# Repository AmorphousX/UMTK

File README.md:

# UMTK
Code for running UMTK

## Indicator LED

- Slow Flash: Not Connected
- Fast Flash: Running
- ON: Jogging
- OFF: Standby

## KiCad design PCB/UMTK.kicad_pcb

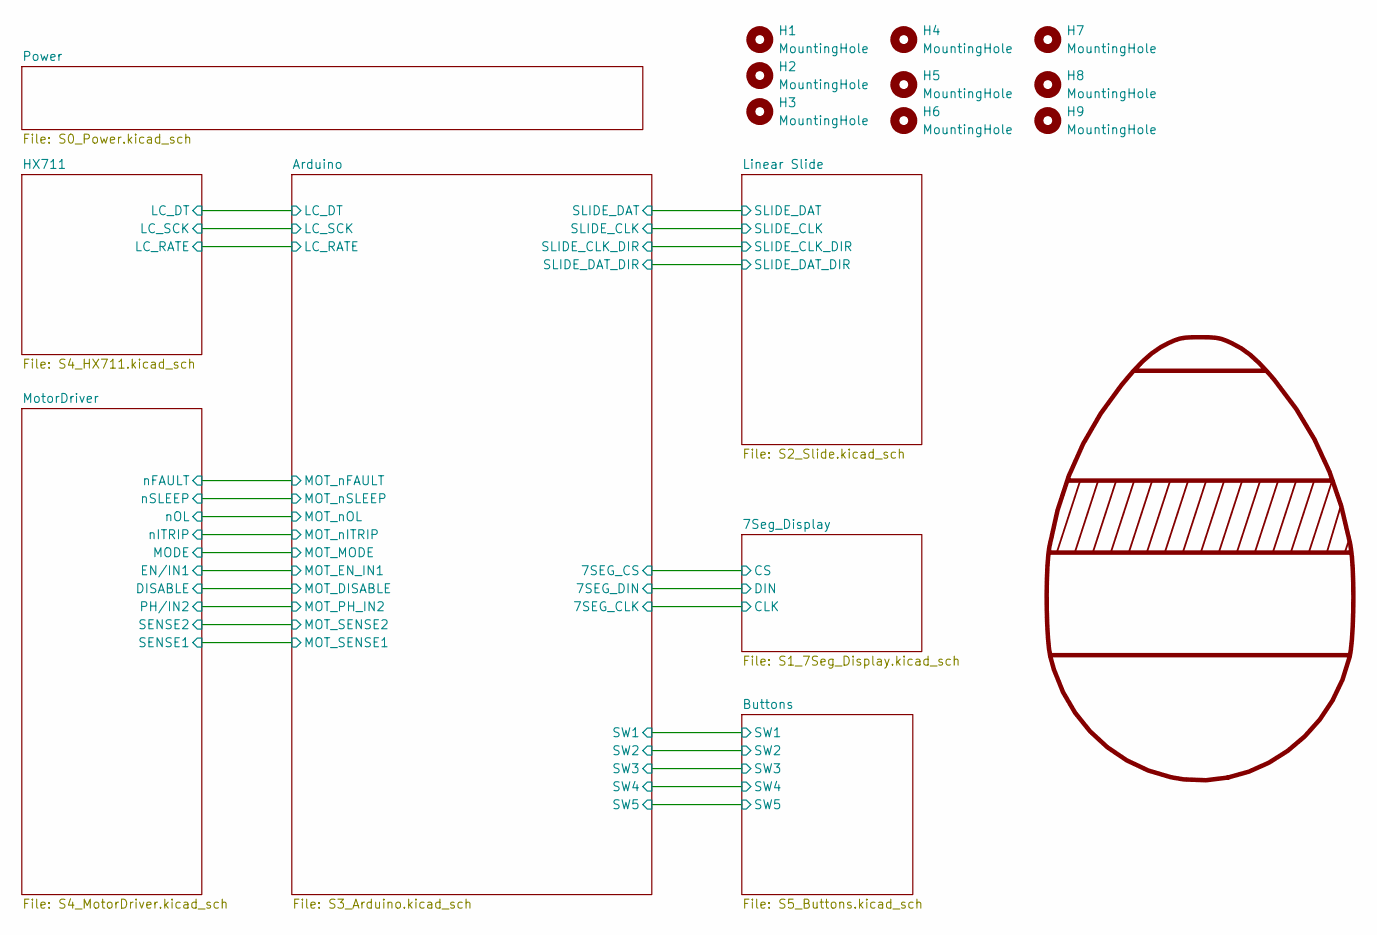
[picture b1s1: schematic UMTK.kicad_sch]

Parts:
G1: Tensile Cat
H1, H2, H3, H4, H5, H6, H7, H8, H9: MountingHole; MountingHole_4mm

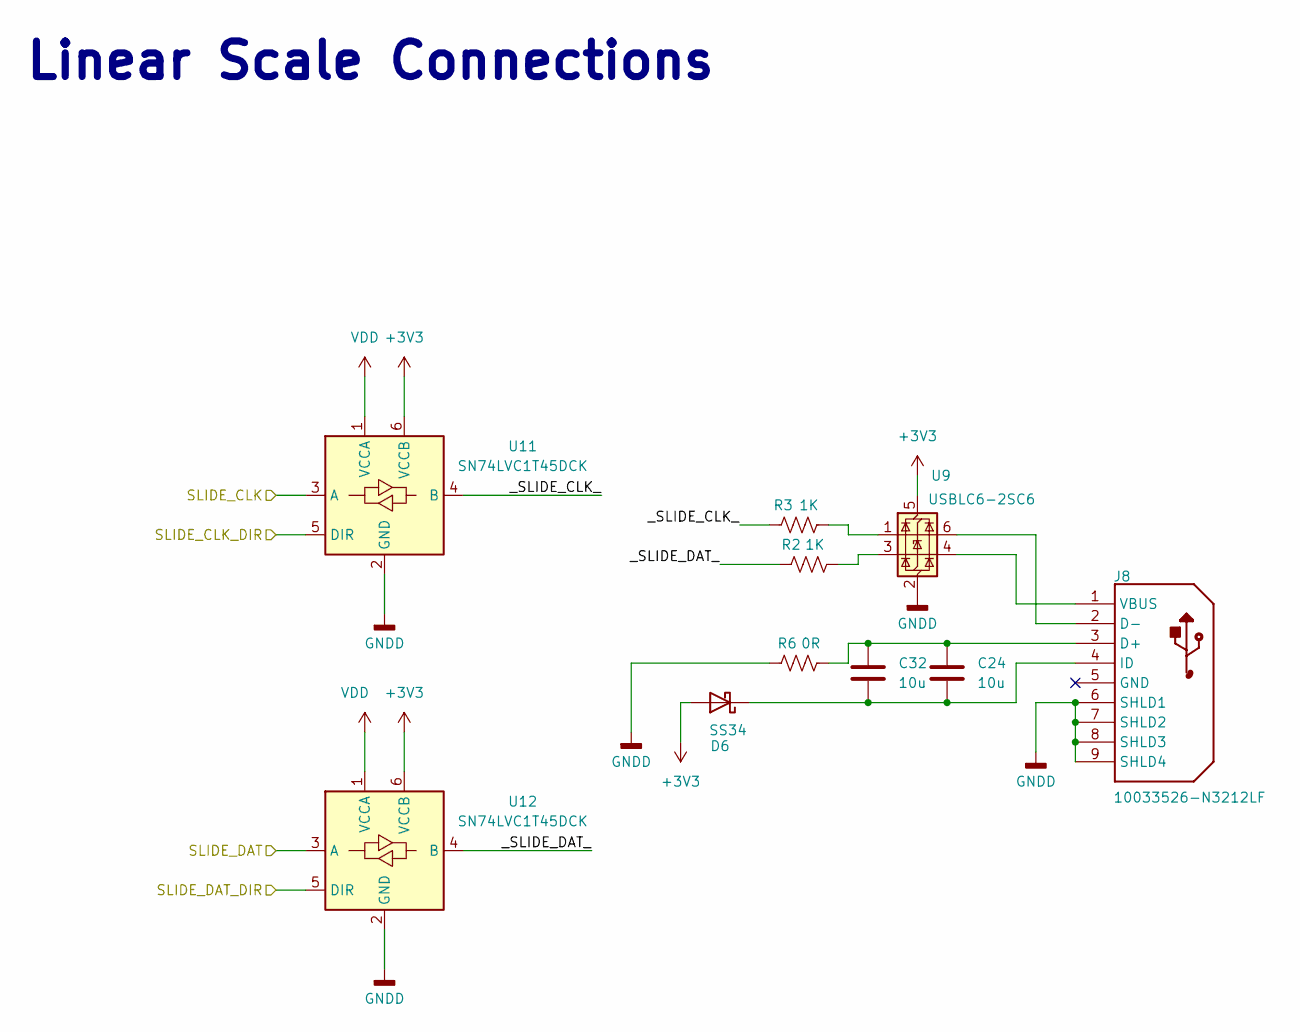
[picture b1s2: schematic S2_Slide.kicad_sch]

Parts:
C24, C32: 10u; C_0805_2012Metric
D6: SS34; D_SMA
J8: 10033526-N3212LF; USB_Mini-B_Wuerth_65100516121_Horizontal; FLAMMABILITY RATING UL 94 V-0; PARTNUMBER 10033526-N3212LF
R2, R3: 1K; R_0603_1608Metric
R6: 0R; R_0603_1608Metric
U9: USBLC6-2SC6; SOT-23-6
U11, U12: SN74LVC1T45DCK; SOT-363_SC-70-6

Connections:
+3V3: D6.2 (A), U9.5 (VBUS), U11.6 (VCCB), U12.6 (VCCB); also elsewhere on the board
+5V: U11.1 (VCCA), U12.1 (VCCA); also elsewhere on the board
/Arduino/D3: U11.3 (A); also elsewhere on the board
/Arduino/D4: U12.3 (A); also elsewhere on the board
/Arduino/D23: U11.5 (DIR); also elsewhere on the board
/Arduino/D24: U12.5 (DIR); also elsewhere on the board
/Linear Slide/_SLIDE_CLK_: R3.1, U11.4 (B)
/Linear Slide/_SLIDE_DAT_: R2.1, U12.4 (B)
GNDA: J8.6 (SHLD1), J8.7 (SHLD2), J8.8 (SHLD3), J8.9 (SHLD4), R6.1, U9.2 (GND), U11.2 (GND), U12.2 (GND); also elsewhere on the board
unnamed: C24.1, C32.1, D6.1 (K), J8.4 (ID)
unnamed: C24.2, C32.2, J8.3 (D+), R6.2
unnamed: J8.2 (D-), U9.6 (I/O1)
unnamed: J8.1 (VBUS), U9.4 (I/O2)
unnamed: R2.2, U9.3 (I/O2)
unnamed: R3.2, U9.1 (I/O1)

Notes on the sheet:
Linear Scale Connections

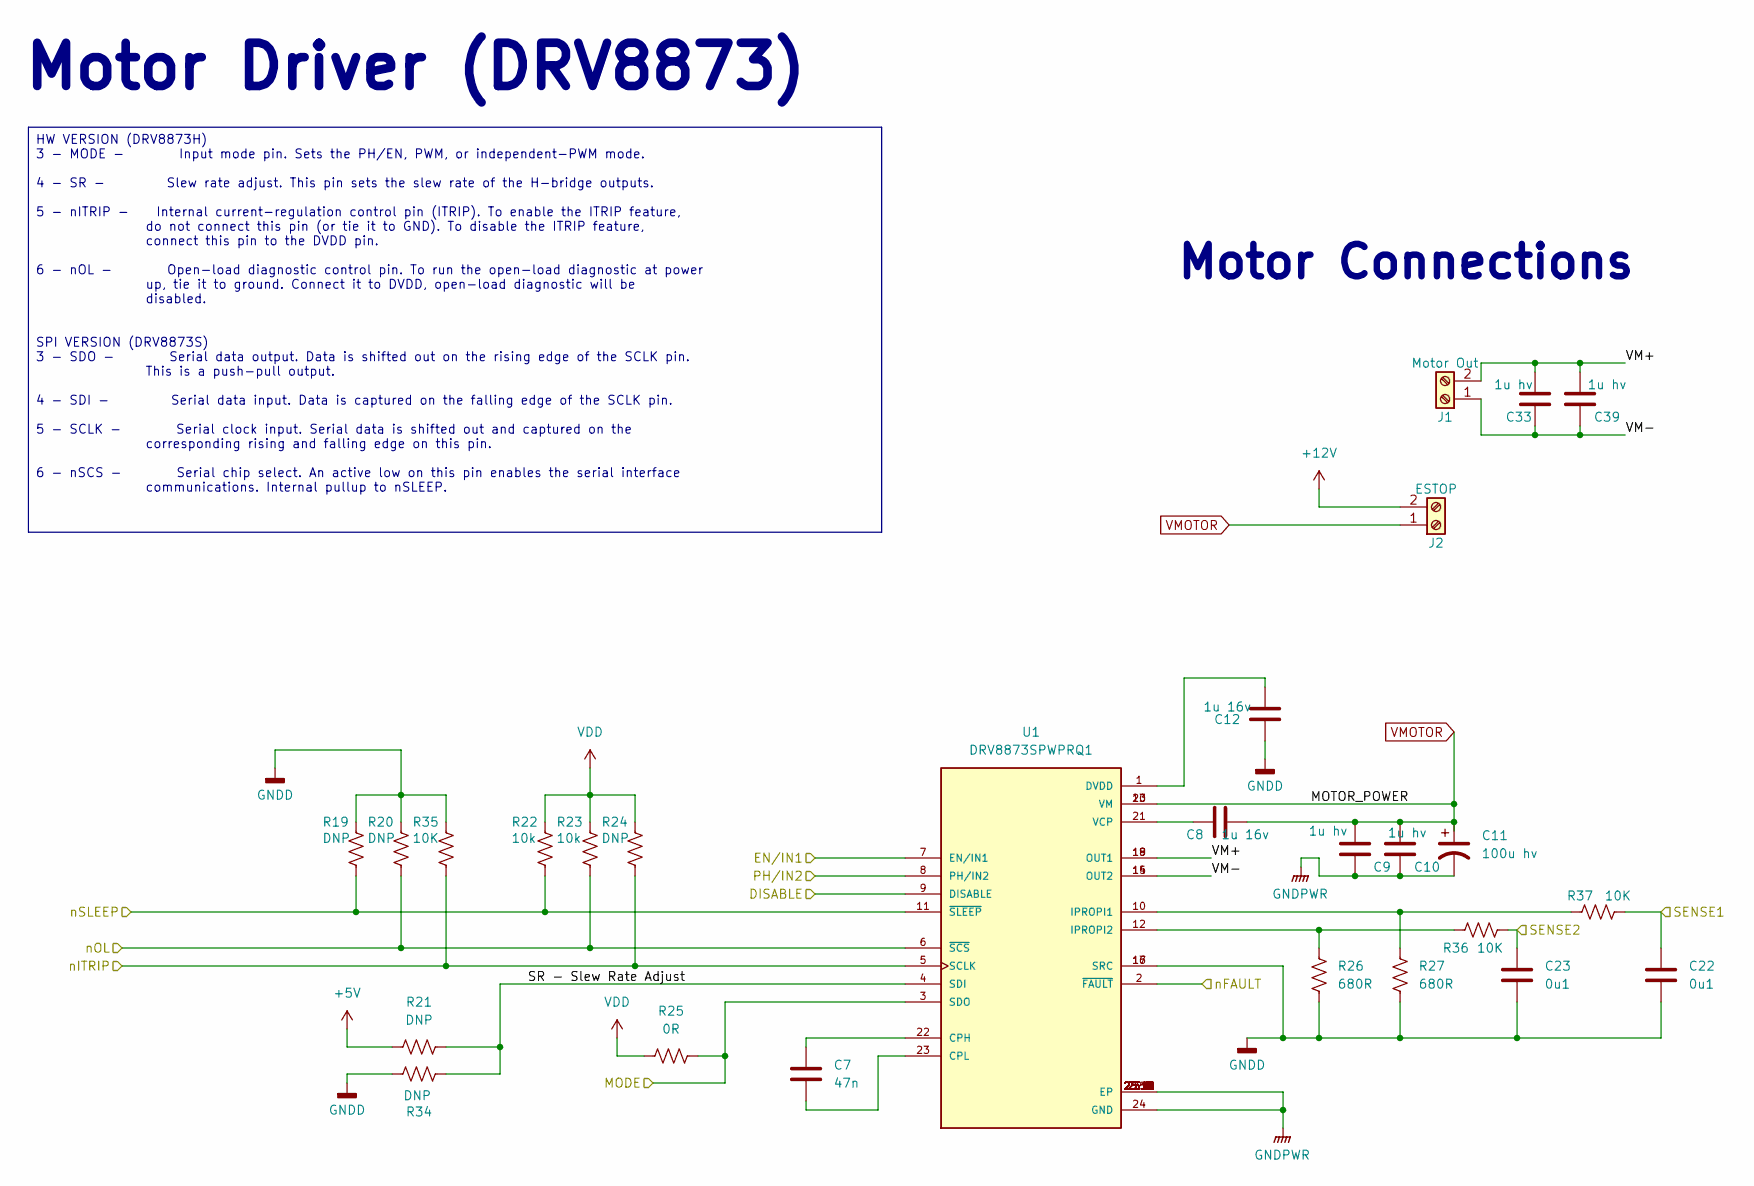
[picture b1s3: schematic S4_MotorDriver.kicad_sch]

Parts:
C7: 47n; C_0603_1608Metric
C8, C12: 1u 16v; C_0603_1608Metric
C9, C10, C33, C39: 1u hv; C_1206_3216Metric
C11: 100u hv; CP_Elec_10x10.5
C22, C23: 0u1; C_0603_1608Metric
J1: Motor Out; PhoenixContact_MC_1,5_2-G-3.81_1x02_P3.81mm_Horizontal
J2: ESTOP; PhoenixContact_MSTBA_2,5_2-G-5,08_1x02_P5.08mm_Horizontal
R19, R20, R21, R24, R34: DNP; R_0603_1608Metric
R22, R23: 10k; R_0603_1608Metric
R25: 0R; R_0603_1608Metric
R26, R27: 680R; R_0603_1608Metric
R35, R36, R37: 10K; R_0603_1608Metric
U1: DRV8873SPWPRQ1; HTSSOP-24-1EP_4.4x7.8mm_P0.65mm_EP3.4x7.8mm_Mask2.4x4.68mm_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; PARTREV A

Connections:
+5V: R21.2, R22.2, R23.2, R24.2, R25.1; also elsewhere on the board
+12V: J2.2; also elsewhere on the board
/Arduino/A2: C22.1, R37.2; also elsewhere on the board
/Arduino/A3: C23.1, R36.2; also elsewhere on the board
/Arduino/D7: U1.9 (DISABLE); also elsewhere on the board
/Arduino/D8: U1.7 (EN/IN1); also elsewhere on the board
/Arduino/D9: U1.8 (PH/IN2); also elsewhere on the board
/Arduino/D10: R24.1, R35.1, U1.5 (SCLK); also elsewhere on the board
/Arduino/D11: R20.1, R23.1, U1.6 (~SCS); also elsewhere on the board
/Arduino/D12: U1.2 (~FAULT); also elsewhere on the board
/Arduino/D14: R19.1, R22.1, U1.11 (~SLEEP); also elsewhere on the board
/Arduino/D22: R25.2, U1.3 (SDO); also elsewhere on the board
/MotorDriver/SR - Slew Rate Adjust: R21.1, R34.2, U1.4 (SDI)
/MotorDriver/VM+: C33.2, C39.2, J1.2, U1.18 (OUT1), U1.19 (OUT1)
/MotorDriver/VM-: C33.1, C39.1, J1.1, U1.14 (OUT2), U1.15 (OUT2)
GNDA: C9.1, C10.1, C11.2, C12.2, C22.2, C23.2, R19.2, R20.2, R26.1, R27.1, R34.1, R35.2, U1.16 (SRC), U1.17 (SRC), U1.24 (GND), U1.25 (EP), U1.25.1 (EP), U1.25.2 (EP), U1.25.3 (EP), U1.25.4 (EP), U1.25.5 (EP), U1.25.6 (EP), U1.25.7 (EP), U1.25.8 (EP), U1.25.9 (EP), U1.25.10 (EP), U1.25.11 (EP), U1.25.12 (EP), U1.25.13 (EP), U1.25.14 (EP), U1.25.15 (EP), U1.25.16 (EP), U1.25.17 (EP), U1.25.18 (EP); also elsewhere on the board
unnamed: C7.1, U1.22 (CPH)
unnamed: C7.2, U1.23 (CPL)
unnamed: C12.1, U1.1 (DVDD)
unnamed: R27.2, R37.1, U1.10 (IPROPI1)
unnamed: R26.2, R36.1, U1.12 (IPROPI2)
unnamed: C8.1, U1.21 (VCP)
VMOTOR: C8.2, C9.2, C10.2, C11.1, J2.1, U1.13 (VM), U1.20 (VM); also elsewhere on the board

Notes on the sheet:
Motor Connections
Motor Driver (DRV8873)
HW VERSION (DRV8873H) 3 - MODE - Input mode pin. Sets the PH/EN, PWM, or independent-PWM mode. 4 - SR - Slew rate adjust. This pin sets the slew rate of the H-bridge outputs. 5 - nITRIP - Internal current-regulation control pin (ITRIP). To enable the ITRIP feature, do not connect this pin (or tie i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

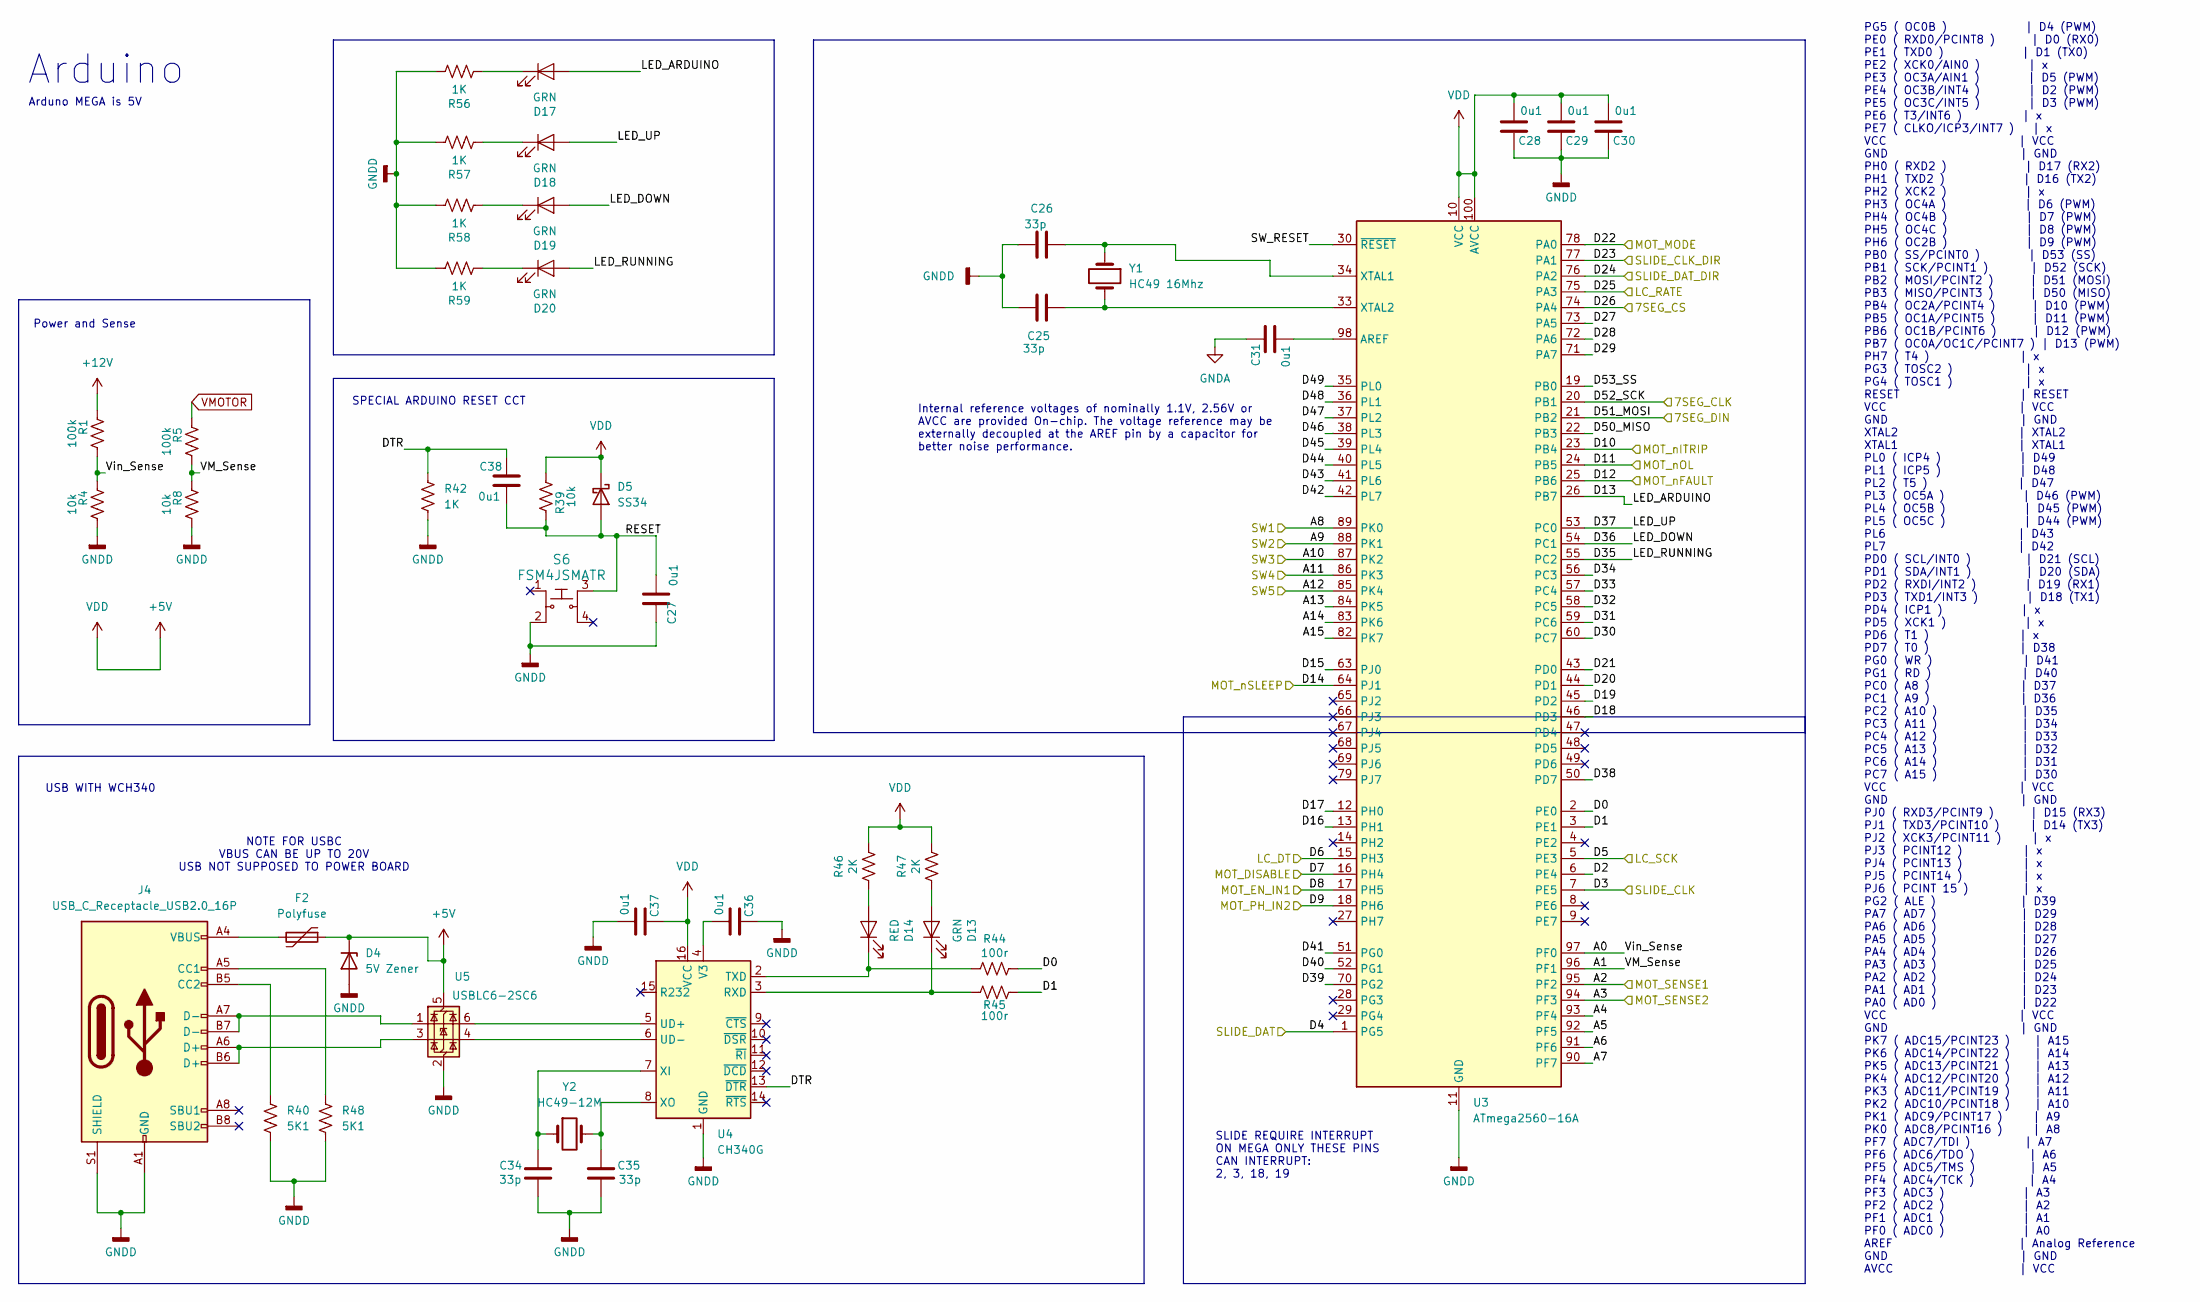
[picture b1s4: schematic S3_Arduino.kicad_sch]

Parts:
C25, C26, C34, C35: 33p; C_0603_1608Metric
C27, C28, C29, C30, C31, C36, C37, C38: 0u1; C_0603_1608Metric
D4: 5V Zener; D_SOD-523
D5: SS34; D_SMA
D13, D17, D18, D19, D20: GRN; LED_0603_1608Metric
D14: RED; LED_0603_1608Metric
F2: Polyfuse; Fuse_1206_3216Metric
J4: USB_C_Receptacle_USB2.0_16P; USB_C_Receptacle_HCTL_HC-TYPE-C-16P-01A
R1, R5: 100k; R_0603_1608Metric
R4, R8, R39: 10k; R_0603_1608Metric
R40, R48: 5K1; R_0603_1608Metric
R42, R56, R57, R58, R59: 1K; R_0603_1608Metric
R44, R45: 100r; R_0603_1608Metric
R46, R47: 2K; R_0603_1608Metric
S6: FSM4JSMATR; Switch_Tactile_SMD_6x6mm; MPN FSM4JSMATR; Digi-Key_PN 450-1759-1-ND
U3: ATmega2560-16A; TQFP-100_14x14mm_P0.5mm
U4: CH340G; SOIC-16_3.9x9.9mm_P1.27mm
U5: USBLC6-2SC6; SOT-23-6
Y1: HC49 16Mhz; Crystal_SMD_HC49-SD
Y2: HC49-12M; Crystal_SMD_HC49-SD

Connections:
+5V: C28.2, C29.2, C30.2, C37.1, D4.1 (K), D5.1 (K), F2.1, R39.2, R46.2, R47.2, U3.10 (VCC), U3.31 (VCC), U3.61 (VCC), U3.80 (VCC), U3.100 (AVCC), U4.16 (VCC), U5.5 (VBUS); also elsewhere on the board
+12V: R1.1; also elsewhere on the board
/Arduino/A0: R1.2, R4.1, U3.97 (PF0)
/Arduino/A1: R5.2, R8.1, U3.96 (PF1)
/Arduino/A2: U3.95 (PF2); also elsewhere on the board
/Arduino/A3: U3.94 (PF3); also elsewhere on the board
/Arduino/A4: U3.93 (PF4)
/Arduino/A5: U3.92 (PF5)
/Arduino/A6: U3.91 (PF6)
/Arduino/A7: U3.90 (PF7)
/Arduino/A8: U3.89 (PK0); also elsewhere on the board
/Arduino/A9: U3.88 (PK1); also elsewhere on the board
/Arduino/A10: U3.87 (PK2); also elsewhere on the board
/Arduino/A11: U3.86 (PK3); also elsewhere on the board
/Arduino/A12: U3.85 (PK4); also elsewhere on the board
/Arduino/A13: U3.84 (PK5)
/Arduino/A14: U3.83 (PK6)
/Arduino/A15: U3.82 (PK7)
/Arduino/D0: R44.2, U3.2 (PE0)
/Arduino/D1: R45.2, U3.3 (PE1)
/Arduino/D2: U3.6 (PE4)
/Arduino/D3: U3.7 (PE5); also elsewhere on the board
/Arduino/D4: U3.1 (PG5); also elsewhere on the board
/Arduino/D5: U3.5 (PE3); also elsewhere on the board
/Arduino/D6: U3.15 (PH3); also elsewhere on the board
/Arduino/D7: U3.16 (PH4); also elsewhere on the board
/Arduino/D8: U3.17 (PH5); also elsewhere on the board
/Arduino/D9: U3.18 (PH6); also elsewhere on the board
/Arduino/D10: U3.23 (PB4); also elsewhere on the board
/Arduino/D11: U3.24 (PB5); also elsewhere on the board
/Arduino/D12: U3.25 (PB6); also elsewhere on the board
/Arduino/D13: D17.2 (A), U3.26 (PB7)
/Arduino/D14: U3.64 (PJ1); also elsewhere on the board
/Arduino/D15: U3.63 (PJ0)
/Arduino/D16: U3.13 (PH1)
/Arduino/D17: U3.12 (PH0)
/Arduino/D18: U3.46 (PD3)
/Arduino/D19: U3.45 (PD2)
/Arduino/D20: U3.44 (PD1)
/Arduino/D21: U3.43 (PD0)
/Arduino/D22: U3.78 (PA0); also elsewhere on the board
/Arduino/D23: U3.77 (PA1); also elsewhere on the board
/Arduino/D24: U3.76 (PA2); also elsewhere on the board
/Arduino/D25: U3.75 (PA3); also elsewhere on the board
/Arduino/D26: U3.74 (PA4); also elsewhere on the board
/Arduino/D27: U3.73 (PA5)
/Arduino/D28: U3.72 (PA6)
/Arduino/D29: U3.71 (PA7)
/Arduino/D30: U3.60 (PC7)
/Arduino/D31: U3.59 (PC6)
/Arduino/D32: U3.58 (PC5)
/Arduino/D33: U3.57 (PC4)
/Arduino/D34: U3.56 (PC3)
/Arduino/D35: D20.2 (A), U3.55 (PC2)
/Arduino/D36: D19.2 (A), U3.54 (PC1)
/Arduino/D37: D18.2 (A), U3.53 (PC0)
/Arduino/D38: U3.50 (PD7)
/Arduino/D39: U3.70 (PG2)
/Arduino/D40: U3.52 (PG1)
/Arduino/D41: U3.51 (PG0)
/Arduino/D42: U3.42 (PL7)
/Arduino/D43: U3.41 (PL6)
/Arduino/D44: U3.40 (PL5)
/Arduino/D45: U3.39 (PL4)
/Arduino/D46: U3.38 (PL3)
/Arduino/D47: U3.37 (PL2)
/Arduino/D48: U3.36 (PL1)
/Arduino/D49: U3.35 (PL0)
/Arduino/D50_MISO: U3.22 (PB3)
/Arduino/D51_MOSI: U3.21 (PB2); also elsewhere on the board
/Arduino/D52_SCK: U3.20 (PB1); also elsewhere on the board
/Arduino/D53_SS: U3.19 (PB0)
/Arduino/DTR: C38.1, R42.1, U4.13 (~DTR)
/Arduino/RESET: C27.2, C38.2, D5.2 (A), R39.1, S6.3
/Arduino/SW_RESET: U3.30 (~RESET)
GNDA: C25.1, C26.1, C27.1, C28.1, C29.1, C30.1, C31.1, C34.1, C35.1, C36.1, C37.2, D4.2 (A), J4.A1 (GND), J4.A12 (GND), J4.B1 (GND), J4.B12 (GND), J4.S1 (SHIELD), R4.2, R8.2, R40.2, R42.2, R48.2, R56.1, R57.1, R58.1, R59.1, S6.2, U3.11 (GND), U3.32 (GND), U3.62 (GND), U3.81 (GND), U3.99 (GND), U4.1 (GND), U5.2 (GND); also elsewhere on the board
unnamed: D13.2 (A), R47.1
unnamed: D13.1 (K), R45.1, U4.3 (RXD)
unnamed: D14.2 (A), R46.1
unnamed: D14.1 (K), R44.1, U4.2 (TXD)
unnamed: D17.1 (K), R56.2
unnamed: D18.1 (K), R57.2
unnamed: D19.1 (K), R58.2
unnamed: D20.1 (K), R59.2
unnamed: F2.2, J4.A4 (VBUS), J4.A9 (VBUS), J4.B4 (VBUS), J4.B9 (VBUS)
unnamed: J4.A5 (CC1), R48.1
unnamed: J4.B5 (CC2), R40.1
unnamed: J4.A6 (D+), J4.B6 (D+), U5.3 (I/O2)
unnamed: J4.A7 (D-), J4.B7 (D-), U5.1 (I/O1)
unnamed: C31.2, U3.98 (AREF)
unnamed: C26.2, U3.34 (XTAL1), Y1.1
unnamed: C25.2, U3.33 (XTAL2), Y1.2
unnamed: U4.5 (UD+), U5.6 (I/O1)
unnamed: U4.6 (UD-), U5.4 (I/O2)
unnamed: C36.2, U4.4 (V3)
unnamed: C34.2, U4.7 (XI), Y2.1
unnamed: C35.2, U4.8 (XO), Y2.2
VMOTOR: R5.1; also elsewhere on the board

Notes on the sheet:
Internal reference voltages of nominally 1.1V, 2.56V or AVCC are provided On-chip. The voltage reference may be externally decoupled at the AREF pin by a capacitor for better noise performance.
NOTE FOR USBC VBUS CAN BE UP TO 20V USB NOT SUPPOSED TO POWER BOARD
Arduno MEGA is 5V
Arduino
SLIDE REQUIRE INTERRUPT ON MEGA ONLY THESE PINS CAN INTERRUPT: 2, 3, 18, 19
USB WITH WCH340
SPECIAL ARDUINO RESET CCT
Power and Sense
PG5 ( OC0B ) | D4 (PWM) PE0 ( RXD0/PCINT8 ) | D0 (RX0) PE1 ( TXD0 ) | D1 (TX0) PE2 ( XCK0/AIN0 ) | x PE3 ( OC3A/AIN1 ) | D5 (PWM) PE4 ( OC3B/INT4 ) | D2 (PWM) PE5 ( OC3C/INT5 ) | D3 (PWM) PE6 ( T3/INT6 ) | x PE7 ( CLKO/ICP3/INT7 ) | x VCC | VCC GND | GND PH0 ( RXD2 ) | D17 (RX2) PH1 ( TXD2 ) | D16 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

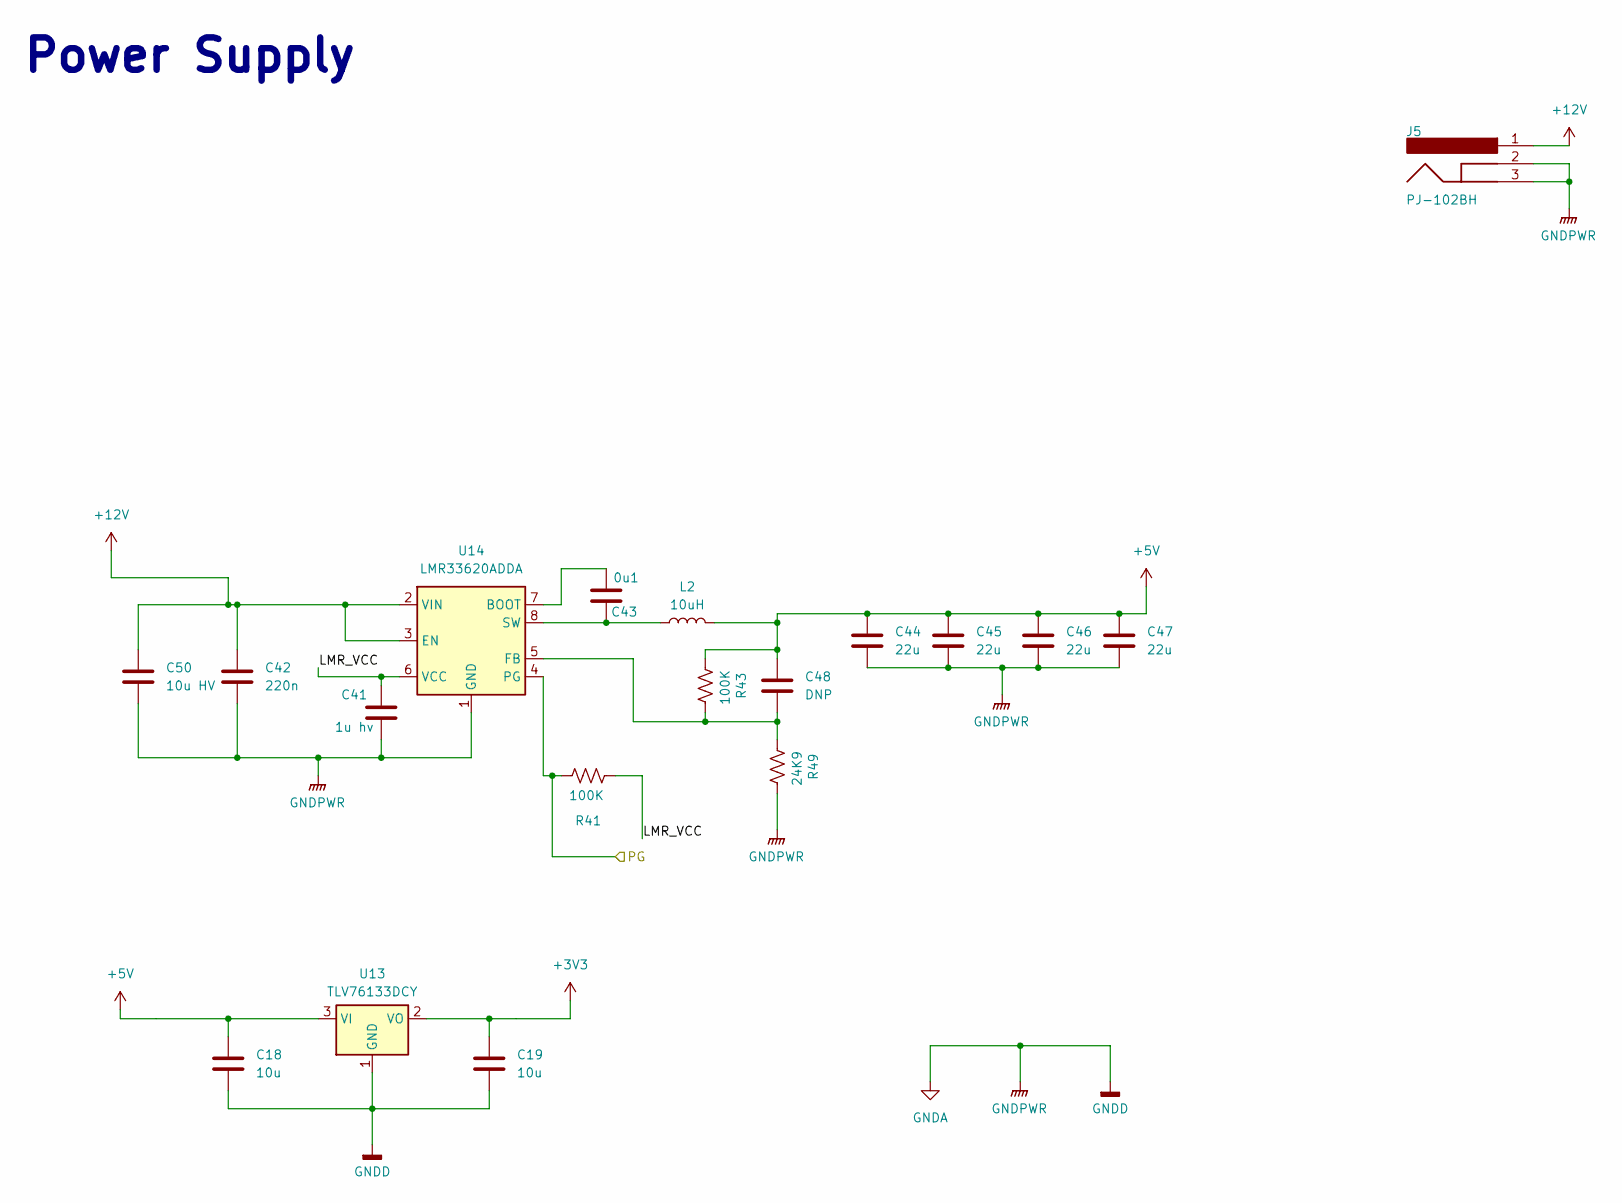
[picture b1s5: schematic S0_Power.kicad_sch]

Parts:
C18, C19: 10u; C_0805_2012Metric
C41: 1u hv; C_0603_1608Metric
C42: 220n; C_0603_1608Metric
C43: 0u1; C_0603_1608Metric
C44, C45, C46, C47: 22u; C_1210_3225Metric
C48: DNP; C_0603_1608Metric
C50: 10u HV; C_1210_3225Metric
J5: PJ-102BH; Barrel_Jack_5.5mmODx2.1mmID_PJ-202A; CURRENT RATING 5A; FLAMMABILITY RATING UL94V-0
L2: 10uH; L_Changjiang_FXL0630
R41, R43: 100K; R_0603_1608Metric
R49: 24K9; R_0603_1608Metric
U13: TLV76133DCY; SOT-223-3_TabPin2
U14: LMR33620ADDA; Texas_HSOP-8-1EP_3.9x4.9mm_P1.27mm_ThermalVias

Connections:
+3V3: C19.2, U13.2 (VO); also elsewhere on the board
+5V: C18.2, C44.1, C45.1, C46.1, C47.1, C48.2, L2.2, R43.2, U13.3 (VI); also elsewhere on the board
+12V: C42.1, C50.1, J5.1, U14.2 (VIN), U14.3 (EN); also elsewhere on the board
/Power/LMR_VCC: C41.1, R41.2, U14.6 (VCC)
/Power/PG: R41.1, U14.4 (PG)
GNDA: C18.1, C19.1, C41.2, C42.2, C44.2, C45.2, C46.2, C47.2, C50.2, J5.2, J5.3, R49.1, U13.1 (GND), U14.1 (GND), U14.9 (GND); also elsewhere on the board
unnamed: C43.2, U14.7 (BOOT)
unnamed: C48.1, R43.1, R49.2, U14.5 (FB)
unnamed: C43.1, L2.1, U14.8 (SW)

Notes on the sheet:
Power Supply

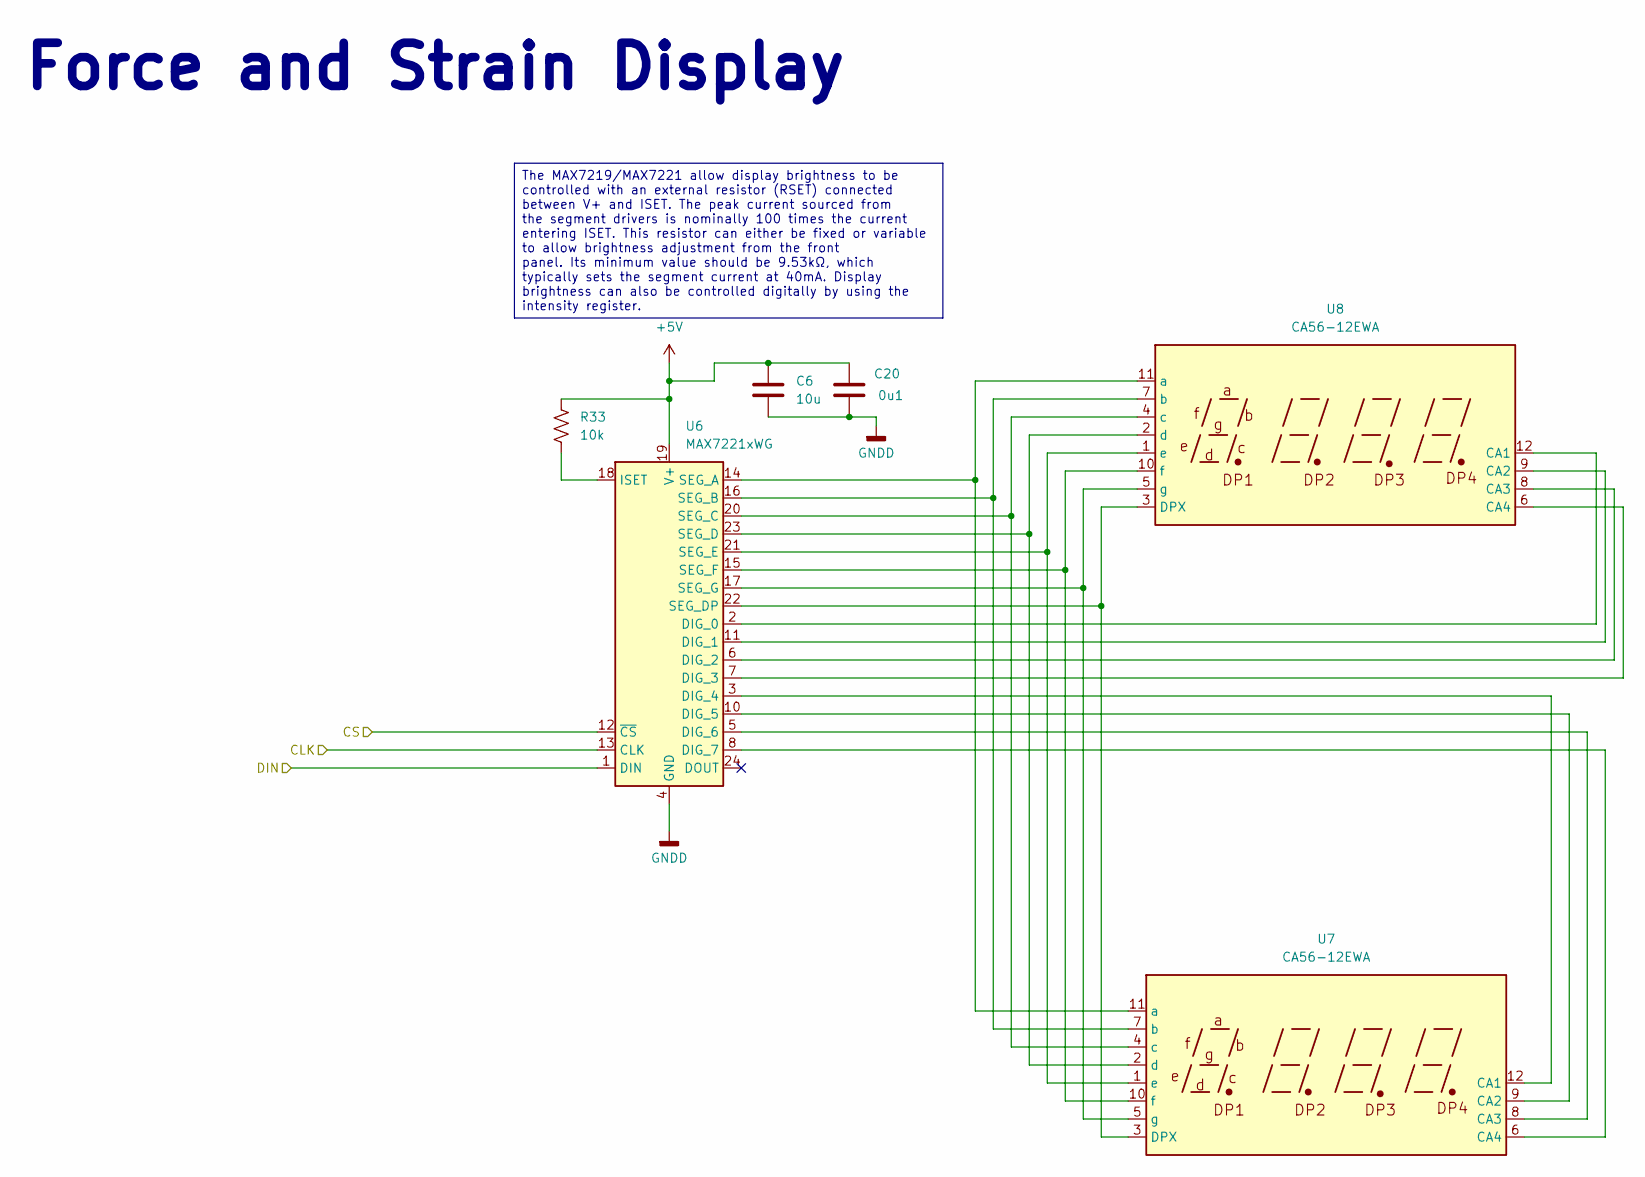
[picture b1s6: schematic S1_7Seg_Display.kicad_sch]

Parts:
C6: 10u; C_0805_2012Metric
C20: 0u1; C_0603_1608Metric
R33: 10k; R_0603_1608Metric
U6: MAX7221xWG; SOIC-24W_7.5x15.4mm_P1.27mm
U7, U8: CA56-12EWA

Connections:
+5V: C6.2, C20.2, R33.1, U6.19 (V+); also elsewhere on the board
/Arduino/D26: U6.12 (~CS); also elsewhere on the board
/Arduino/D51_MOSI: U6.1 (DIN); also elsewhere on the board
/Arduino/D52_SCK: U6.13 (CLK); also elsewhere on the board
GNDA: C6.1, C20.1, U6.4 (GND), U6.9 (GND); also elsewhere on the board
unnamed: U6.2 (DIG_0), U8.12 (CA1)
unnamed: U6.11 (DIG_1), U8.9 (CA2)
unnamed: U6.6 (DIG_2), U8.8 (CA3)
unnamed: U6.7 (DIG_3), U8.6 (CA4)
unnamed: U6.3 (DIG_4), U7.12 (CA1)
unnamed: U6.10 (DIG_5), U7.9 (CA2)
unnamed: U6.5 (DIG_6), U7.8 (CA3)
unnamed: U6.8 (DIG_7), U7.6 (CA4)
unnamed: R33.2, U6.18 (ISET)
unnamed: U6.14 (SEG_A), U7.11 (a), U8.11 (a)
unnamed: U6.16 (SEG_B), U7.7 (b), U8.7 (b)
unnamed: U6.20 (SEG_C), U7.4 (c), U8.4 (c)
unnamed: U6.23 (SEG_D), U7.2 (d), U8.2 (d)
unnamed: U6.22 (SEG_DP), U7.3 (DPX), U8.3 (DPX)
unnamed: U6.21 (SEG_E), U7.1 (e), U8.1 (e)
unnamed: U6.15 (SEG_F), U7.10 (f), U8.10 (f)
unnamed: U6.17 (SEG_G), U7.5 (g), U8.5 (g)

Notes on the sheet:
Force and Strain Display
The MAX7219/MAX7221 allow display brightness to be controlled with an external resistor (RSET) connected between V+ and ISET. The peak current sourced from the segment drivers is nominally 100 times the current entering ISET. This resistor can either be fixed or variable to allow brightness adjustm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

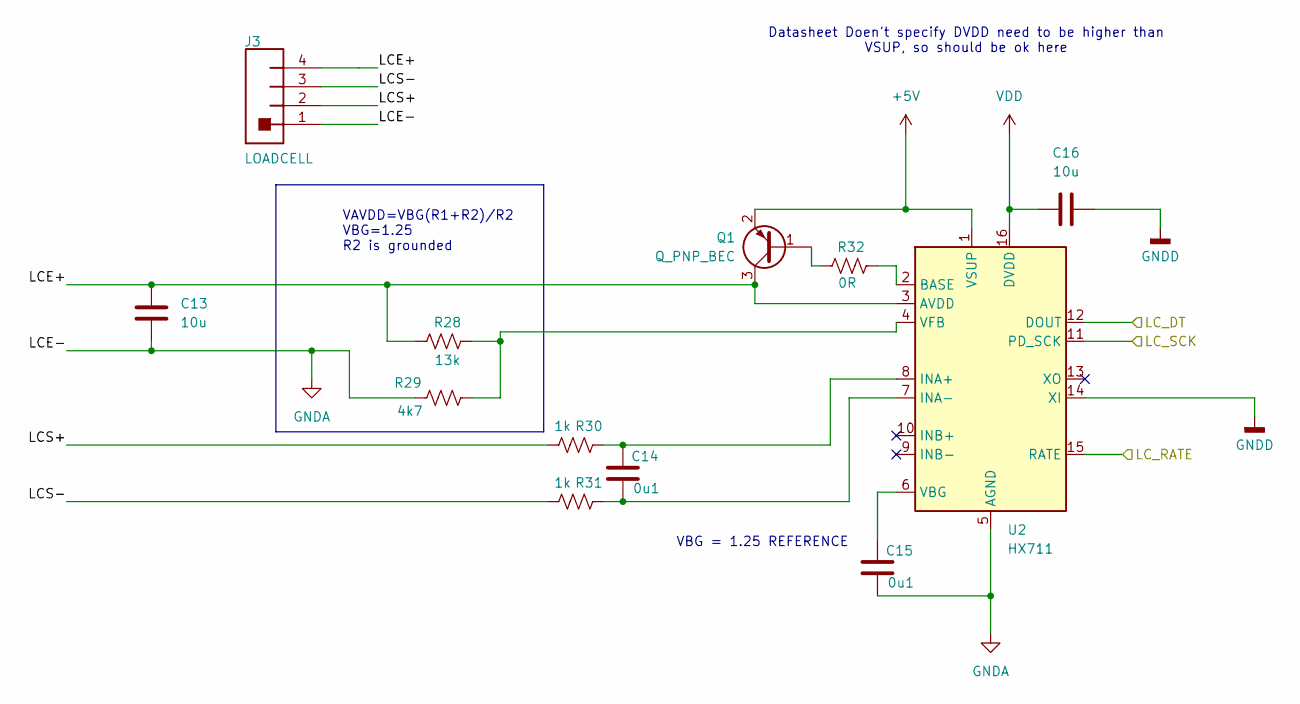
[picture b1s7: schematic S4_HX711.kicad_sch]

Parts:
C13, C16: 10u; C_0805_2012Metric
C14, C15: 0u1; C_0603_1608Metric
J3: LOADCELL; PhoenixContact_MC_1,5_4-G-3.81_1x04_P3.81mm_Horizontal
Q1: Q_PNP_BEC; SOT-23
R28: 13k; C_0603_1608Metric
R29: 4k7; R_0603_1608Metric
R30, R31: 1k; R_0603_1608Metric
R32: 0R; R_0603_1608Metric
U2: HX711; SOP-16_3.9x9.9mm_P1.27mm

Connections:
+5V: C16.1, Q1.2 (E), U2.1 (VSUP), U2.16 (DVDD); also elsewhere on the board
/Arduino/D5: U2.11 (PD_SCK); also elsewhere on the board
/Arduino/D6: U2.12 (DOUT); also elsewhere on the board
/Arduino/D25: U2.15 (RATE); also elsewhere on the board
/HX711/LCE+: C13.2, J3.4, Q1.3 (C), R28.1, U2.3 (AVDD)
/HX711/LCS+: J3.2, R30.1
/HX711/LCS-: J3.3, R31.1
GNDA: C13.1, C15.2, C16.2, J3.1, R29.1, U2.5 (AGND), U2.14 (XI); also elsewhere on the board
unnamed: Q1.1 (B), R32.1
unnamed: R32.2, U2.2 (BASE)
unnamed: C14.1, R30.2, U2.8 (INA+)
unnamed: C14.2, R31.2, U2.7 (INA-)
unnamed: C15.1, U2.6 (VBG)
unnamed: R28.2, R29.2, U2.4 (VFB)

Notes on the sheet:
VBG = 1.25 REFERENCE
VAVDD=VBG(R1+R2)/R2 VBG=1.25 R2 is grounded
Datasheet Doen't specify DVDD need to be higher than VSUP, so should be ok here

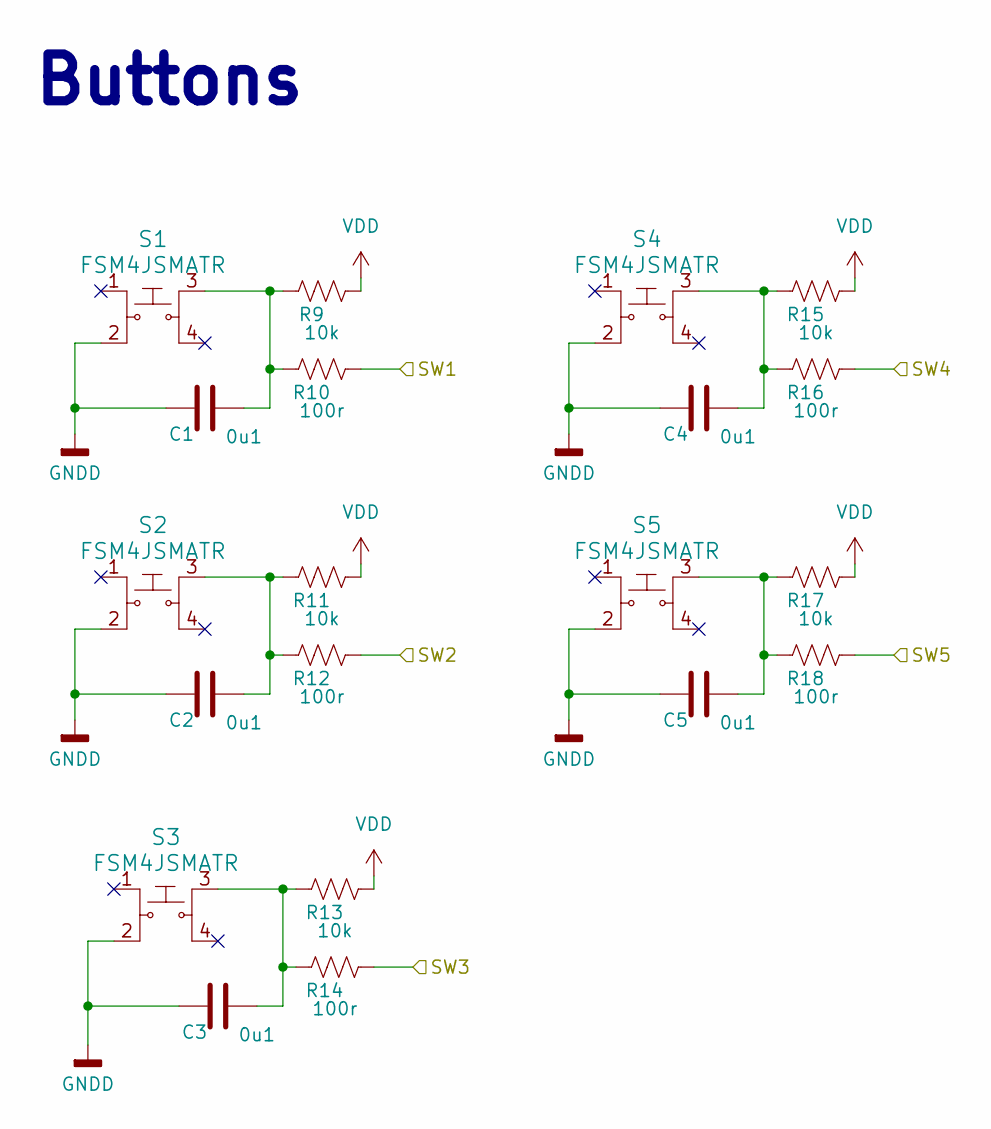
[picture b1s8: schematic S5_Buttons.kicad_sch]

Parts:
C1, C2, C3, C4, C5: 0u1; C_0603_1608Metric
R9, R11, R13, R15, R17: 10k; R_0603_1608Metric
R10, R12, R14, R16, R18: 100r; R_0603_1608Metric
S1, S2, S3, S4, S5: FSM4JSMATR; Switch_Tactile_SMD_6x6mm; MPN FSM4JSMATR; Digi-Key_PN 450-1759-1-ND

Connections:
+5V: R9.2, R11.2, R13.2, R15.2, R17.2; also elsewhere on the board
/Arduino/A8: R10.2; also elsewhere on the board
/Arduino/A9: R12.2; also elsewhere on the board
/Arduino/A10: R14.2; also elsewhere on the board
/Arduino/A11: R16.2; also elsewhere on the board
/Arduino/A12: R18.2; also elsewhere on the board
GNDA: C1.1, C2.1, C3.1, C4.1, C5.1, S1.2, S2.2, S3.2, S4.2, S5.2; also elsewhere on the board
unnamed: C1.2, R9.1, R10.1, S1.3
unnamed: C2.2, R11.1, R12.1, S2.3
unnamed: C3.2, R13.1, R14.1, S3.3
unnamed: C4.2, R15.1, R16.1, S4.3
unnamed: C5.2, R17.1, R18.1, S5.3

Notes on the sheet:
Buttons
